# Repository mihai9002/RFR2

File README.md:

# THE RFR2 - Radio Frequency Receiver 2

## What is it?

The RFR2 is a device that can switch from being an ordinary radio, to being a Bluetooth speaker, with the flip of a switch.

With accesible parts at its core, and most of the wiring job being handled by a PCB, this project is very easy to understand, then assemble.

## Why?

Well, I wanted to make something original, and then I was thinking about getting a Bluetooth speaker. So, why not include a radio module, for when you don't have internet, and give it a modern, minimal design? On top of that, it also forced me to learn how to make a compact PCB, and if you look at the other ones I made, and compare them to this one, I think the goal was at least partially reached. Plus I just loved how it would end up looking, so that was an additional bit of motivation.

## Hardware

### PCB

  Features:

  - Most of the components communicate via I2C. This being the case, volume and channel can be changed using rotary encoders, rather than classic potentiometers.
  - A pin on the microcontroller (Raspberry Pi Pico) detects if there is current flow between the radio module and the 3.3V line. If so, the Pico knows to display "radio mode". If not, it will display "BT mode"
  - The Bluetooth device(JDY-62) does not need any connection to the MCU, so it is just hooked up to the digital amp.
  - The amplifier communicates via I2C, and only one of them handles the amplifying of both of the systems. It leads to 2 5cm speakers
  - A battery pack made uo of a 18650 Li-ion cells should last for a long time, since it has 2500mAh capacity
  - Quality USB-C charger, with overcharge protection
  - STATUS LED!!!
  - Heated inserts, no screws on bare plastic

### Case

  - I love how the case turned out, with the minimal style, especially the grille and the shallow knobs. I tried to shrink it down as much as possible, so it would use up less plastic, and I also removed a lot of unnecessary parts in the final design.

### Firmware

  I don't have much to say about this, since I am very bad at writing code, so I tried my best to make something that would pass as firmware, but I am pretty sure it doesn't work, and I am waiting for the parts, in order to figure it out one component after the other.

## Assembly

Putting the parts together is pretty straightforward:
  - make sure to first load the firmware on the Pico
  -  For the PCB, you just have to solder all the parts in their designated spots, trying to solder directly to the PCB as little as possible, and using female pin headers wherever possible(OLED, Pico, BT module, amp). The PCB can then be secured using the 3d printed clips
  - After that, you should insert all the heated inserts, into their designated holes(the ones that hold the speakers are M4, the rest are M3)
  - The charger can be glued in place 
  - Screw everything in, and you re pretty much done

## AI usage:

AI was used for research, specifically part selection, and for understanding code.

## Bill Of Materials

| Item                   | Description              | Link                                                                                                                                                                                                                                                                                                                                                                                                                                                                                                                                                                                                                                                               | Qty | Price per unit | Total price w/o shipping | Shipping | Total   |
| ---------------------- | ------------------------ | ------------------------------------------------------------------------------------------------------------------------------------------------------------------------------------------------------------------------------------------------------------------------------------------------------------------------------------------------------------------------------------------------------------------------------------------------------------------------------------------------------------------------------------------------------------------------------------------------------------------------------------------------------------------ | --- | -------------- | ------------------------ | -------- | ------- |
| PCB                    | PCB                      | \-                                                                                                                                                                                                                                                                                                                                                                                                                                                                                                                                                                                                                                                                 | 5   |                | 4.54 €                  | 8.88 €  | 13.42 €|
| M4 bolts               | M4 bolts                 | already owned                                                                                                                                                                                                                                                                                                                                                                                                                                                                                                                                                                                                                                                      | 8   | already owned  | 0.00 €                  | 0.00 €  | 0.00 € |
| M4 nuts                | M4 nuts                  | already owned                                                                                                                                                                                                                                                                                                                                                                                                                                                                                                                                                                                                                                                      | 8   | already owned  | 0.00 €                  |          |         |
| M3 bolts               | M3 bolts                 | already owned                                                                                                                                                                                                                                                                                                                                                                                                                                                                                                                                                                                                                                                      | 8   | already owned  | 0.00 €                  |          |         |
| M3 nuts                | M3 nuts                  | already owned                                                                                                                                                                                                                                                                                                                                                                                                                                                                                                                                                                                                                                                      | 8   | already owned  | 0.00 €                  |          |         |
| SMD2835-6500K          | SMD LED                  | [https://electronicmarket.ro](https://electronicmarket.ro/2835-smd-led-6000-6500k-alb?gad_source=1&gad_campaignid=21513542058&gbraid=0AAAAA-D1O9Z2KXrM8jS931hq9EL83sPFJ&gclid=Cj0KCQjw-pHPBhCdARIsAHXYWP_1JeyVaks436fD8OcetfT-7PHea8UyYtYJ8BzN7zg7yd09QDPxtFgaAkwxEALw_wcB)                                                                                                                                                                                                                                                                                                                                                                                                                       | 1   | 0.06 €        | 0.06 €                  | 2.26 €  | 2.69 € |
| SPDT Slide Switch      | ON-ON Slide Switch       | [https://electronicmarket.ro](https://electronicmarket.ro/en-gb/mini-spdt-slide-switch-on-on-3-pin?search=Switch)                                                                                                                                                                                                                                                                                                                                                                                                                                                                                                                                                                                 | 1   | 0.11 €        | 0.11 €                  |          |         |
| SS12D00                | Mini On-Off Slide Switch | [https://electronicmarket.ro](https://electronicmarket.ro/en-gb/switches-and-buttons/slide-switch/ss12d00-mini-on-off-slide-switch)                                                                                                                                                                                                                                                                                                                                                                                                                                                                                                                                                               | 1   | 0.26 €        | 0.26 €                  |          |         |
| 0.90" OLED Display     | Display                  | [https://sigmanortec.ro](https://sigmanortec.ro/display-oled-096-i2c-iic-alb?SubmitCurrency=1&id_currency=3)                                                                                                                                                                                                                                                                                                                                                                                                                                                                                                                                                                                 | 1   | 3.71 €        | 3.71 €                  | 2.96 €  | 10.84 €|
| 433MHz helical antenna | antenna                  | [https://sigmanortec.ro](https://sigmanortec.ro/en/433mhz-helical-antenna)                                                                                                                                                                                                                                                                                                                                                                                                                                                                                                                                                                                                                   | 1   | 0.60 €        | 0.60 €                  |          |         |
| AMS1117 3.3V           | Voltage regulator        | [https://sigmanortec.ro](https://sigmanortec.ro/Modul-coborator-tensiune-AMS1117-3-3V-p134573098?SubmitCurrency=1&id_currency=3)                                                                                                                                                                                                                                                                                                                                                                                                                                                                                                                                                             | 1   | 0.73 €        | 0.73 €                  |          |         |
| TP4056                 | USB-C charger            | [https://sigmanortec.ro](https://sigmanortec.ro/modul-incarcare-baterie-litiu-tp4056-typec-5v-1a-cu-protectie)                                                                                                                                                                                                                                                                                                                                                                                                                                                                                                                                                                               | 1   | 0.93 €        | 0.93 €                  |          |         |
| 18650 Battery holder   | Battery holder           | [https://sigmanortec.ro](https://sigmanortec.ro/Suport-baterie-18650-p158825500)                                                                                                                                                                                                                                                                                                                                                                                                                                                                                                                                                                                                             | 1   | 1.91 €        | 1.91 €                  |          |         |
| TPA2016D2              | Digital Amplifier        | [https://www.aliexpress.com](https://www.aliexpress.com/item/1005007771780893.html?spm=a2g0o.productlist.main.1.1388WFE4WFE4Bm&algo_pvid=e4d26b52-9606-43dc-8250-c23014e96432&algo_exp_id=e4d26b52-9606-43dc-8250-c23014e96432-0&pdp_ext_f=%7B%22order%22%3A%2235%22%2C%22eval%22%3A%221%22%2C%22fromPage%22%3A%22search%22%7D&pdp_npi=6%40dis%21RON%2153.65%2153.65%21%21%2112.06%2112.06%21%40211b617b17774791883722573e4de4%2112000042149628474%21sea%21RO%214338401437%21ABX%211%210%21n_tag%3A-29910%3Bd%3Aab527837%3Bm03_new_user%3A-29895&curPageLogUid=89HHeY0mkhnZ&utparam-url=scene%3Asearch%7Cquery_from%3A%7Cx_object_id%3A1005007771780893%7C_p_origin_prod%3A)                     | 1   | 10.88 €       | 10.88 €                 | 6.63 €  | 24.82 €|
| 18650 Cell             | Battery                  | [https://www.aliexpress.com](https://www.aliexpress.com/item/32793701336.html?spm=a2g0o.productlist.main.1.48a3184fd8KZS5&algo_pvid=00aa3b3f-57ad-4e47-b5c8-92639a2236e0&algo_exp_id=00aa3b3f-57ad-4e47-b5c8-92639a2236e0-0&pdp_ext_f=%7B%22order%22%3A%2223359%22%2C%22spu_best_type%22%3A%22price%22%2C%22eval%22%3A%221%22%2C%22fromPage%22%3A%22search%22%7D&pdp_npi=6%40dis%21EUR%2143.38%2139.52%21%21%2148.46%2144.15%21%40210398e917845014974487700e0ea5%2112000053301585582%21sea%21RO%210%21ABX%211%210%21n_tag%3A-29910%3Bd%3Aab527837%3Bm03_new_user%3A-29895&curPageLogUid=190jBEObcvpL&utparam-url=scene%3Asearch%7Cquery_from%3A%7Cx_object_id%3A32793701336%7C_p_origin_prod%3A) | 1   | 7.31 €        | 7.31 €                  |          |         |
| M4x6x4 heated inserts  | Heated inserts           | [https://www.drot.ro](https://www.drot.ro/platforma-arduino/231181-inserts-filetate-m4x6x6-din-alama.html?cv)                                                                                                                                                                                                                                                                                                                                                                                                                                                                                                                                                                             | 8   | 0.17 €        | 1.36 €                  | 3.81 €  | 6.53 € |
| M3x6x4 heated inserts  | Heated inserts           | [https://www.drot.ro](https://www.drot.ro/platforma-arduino/231208-inserts-filetate-m3x6x4-din-alama.html?cv)                                                                                                                                                                                                                                                                                                                                                                                                                                                                                                                                                                             | 8   | 0.17 €        | 1.36 €                  |          |         |
| JDY-62A                | Bluetooth module         | [https://www.optimusdigital.ro](https://www.optimusdigital.ro/ro/wireless-bluetooth/12433-modul-pentru-transmisie-audio-fara-fir-ble-stereo-jdy-62a.html)                                                                                                                                                                                                                                                                                                                                                                                                                                                                                                                                           | 1   | 2.80 €        | 2.80 €                  | 2.00 €  | 6.60 € |
| RDA5807                | RF Radio Module          | [https://www.optimusdigital.ro](https://www.optimusdigital.ro/ro/wireless-radio-fm/745-modul-radio-fm-rda5807m.html?srsltid=AfmBOooLRyTUZa3x3IrgBiQJtpdNmcl8UkR8Xkw7ODdx6JqKyL7N7ozU])                                                                                                                                                                                                                                                                                                                                                                                                                                                                                                              | 1   | 1.80 €        | 1.80 €                  |          |         |
| Visaton FR 58          | Speaker                  | [https://www.thomann.ro](https://www.thomann.ro/visaton_fr_58.htm)                                                                                                                                                                                                                                                                                                                                                                                                                                                                                                                                                                                                                           | 2   | 8.22 €        | 16.44 €                 | 9.35 €  | 25.79 €|
| Grand Total            |                          |                                                                                                                                                                                                                                                                                                                                                                                                                                                                                                                                                                                                                                                                    |     | |54.80 €       | 35.89 €                      | 90.69 € |

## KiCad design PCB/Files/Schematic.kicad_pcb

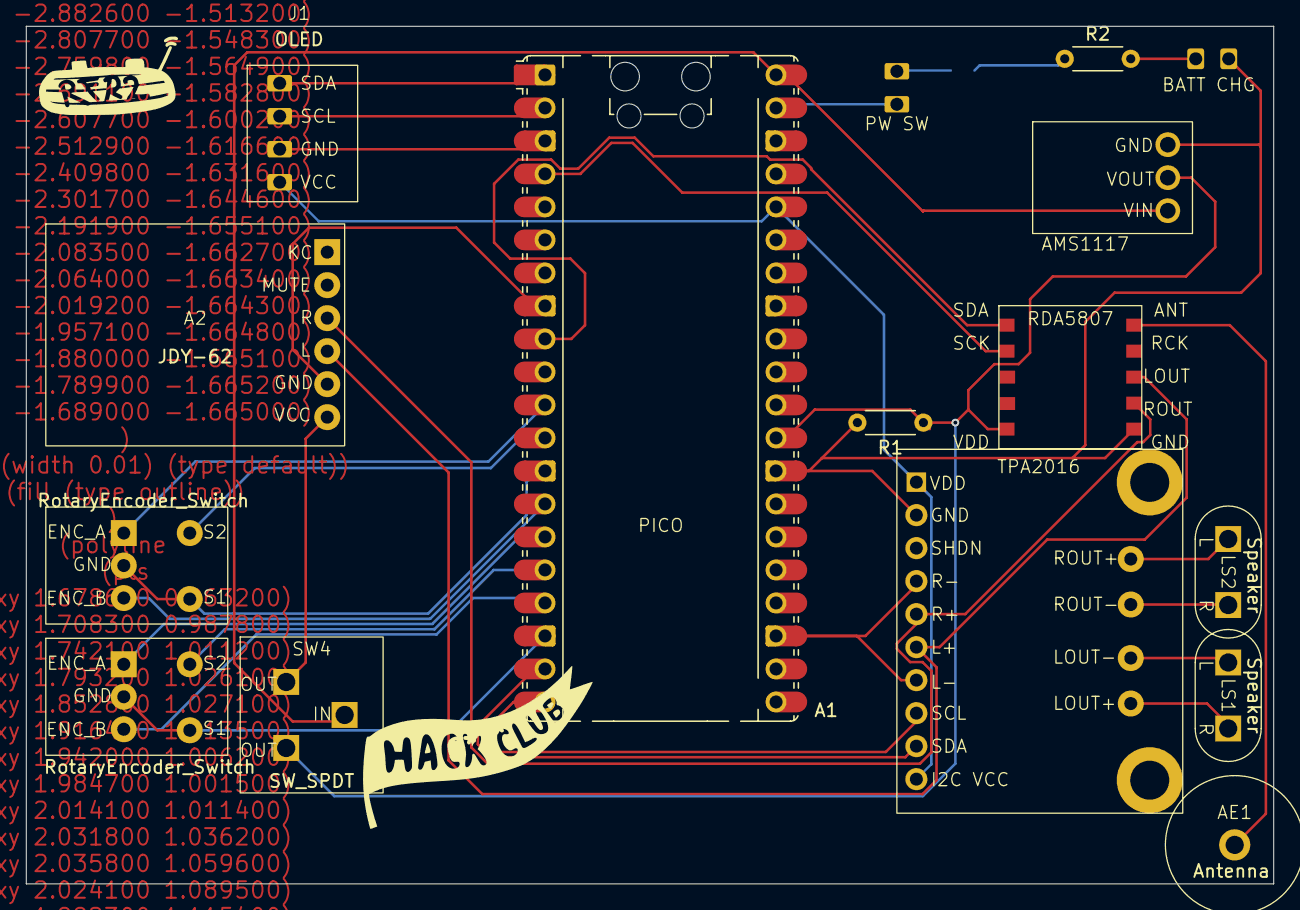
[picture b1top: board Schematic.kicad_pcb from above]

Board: 2 copper layers, 96.0 x 66.0 mm, 17 parts (1 on the bottom side), 27 nets.

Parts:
A1: RaspberryPi_Pico; RaspberryPi_Pico_Common_Unspecified
A2: RaspberryPi_Pico; JDY-62
AE1: Antenna; Antenna hole
AMS1117: AMS1117-3.3; AMS1117-module
BATT CHG: BATTERY
D1: LED; LED_SMD
J1: OLED; SSD1306 simple
LS1, LS2: Speaker; 2pin audio connector
PW SW: SW_DPST_x2; SWITCH
R1, R2: R; R_Axial_DIN0204_L3.6mm_D1.6mm_P5.08mm_Horizontal
RDA5807: RDA5807
SW2, SW3: RotaryEncoder_Switch; R_ENC simple
SW4: SW_SPDT; 2 state switch
TPA2016: TPA2016

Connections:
3.3v: A1.29 (GPIO22), AMS1117.2 (VO), R1.1, RDA5807.5 (VDD), SW4.3 (C)
3V3: A1.36 (3V3), J1.1 (VCC), TPA2016.1 (VDD), TPA2016.9 (I2C_VCC)
5V: A1.40 (VBUS), AMS1117.3 (VI), SW4.2 (B)
5V_IN: A2.6 (VCC), SW4.1 (A)
ENC_A_1: A1.11 (GPIO8), SW2.A
ENC_A_2: A1.15 (GPIO11), SW3.A
ENC_B_1: A1.14 (GPIO10), SW2.B
ENC_B_2: A1.17 (GPIO13), SW3.B
GND: A1.3 (GND), A1.8 (GND), A1.13 (GND), A1.18 (GND), A1.23 (GND), A1.28 (GND), A1.38 (GND), A2.5 (GND), AMS1117.1 (GND), BATT CHG.OUT-, J1.2 (GND), R1.2, RDA5807.6 (GND), SW2.C, SW2.S1, SW3.C, SW3.S1, TPA2016.2 (GND), TPA2016.3 (RGND), TPA2016.6 (LGND)
LEFT: A2.4 (L), RDA5807.8 (LOUT), TPA2016.5 (LIN)
unnamed: AE1.1 (A), RDA5807.10 (ANT)
unnamed: D1.2 (A), R2.1
unnamed: BATT CHG.OUT+, D1.1 (K), PW SW.2 (B), R2.2
unnamed: LS1.2, TPA2016.13 (LOUT+)
unnamed: LS1.1, TPA2016.12 (LOUT-)
unnamed: LS2.1, TPA2016.10 (ROUT+)
unnamed: LS2.2, TPA2016.11 (ROUT-)
RIGHT: A2.3 (R), RDA5807.7 (ROUT), TPA2016.4 (RIN)
SCK: A1.4 (GPIO2), RDA5807.2 (SCK)
SCL: A1.2 (GPIO1), J1.3 (SCL)
SCL_A: A1.20 (GPIO15), TPA2016.7 (SCL)
SDA: A1.1 (GPIO0), J1.4 (SDA)
SDA1: A1.9 (GPIO6), RDA5807.1 (SDA)
SDA_A: A1.19 (GPIO14), TPA2016.8 (SDA)
SWITCH_1: A1.12 (GPIO9), SW2.S2
SWITCH_2: A1.16 (GPIO12), SW3.S2
VSYS: A1.39 (VSYS), PW SW.1 (A)
